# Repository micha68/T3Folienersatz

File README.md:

# T3_Leiterfolie_Ersatz
Ersetzt die Leiterfolie im Instrumententräger

In meinem Fall bei einer Pritsche Bj85, Turbodiesel mit dynamischer Ölkontrolle.

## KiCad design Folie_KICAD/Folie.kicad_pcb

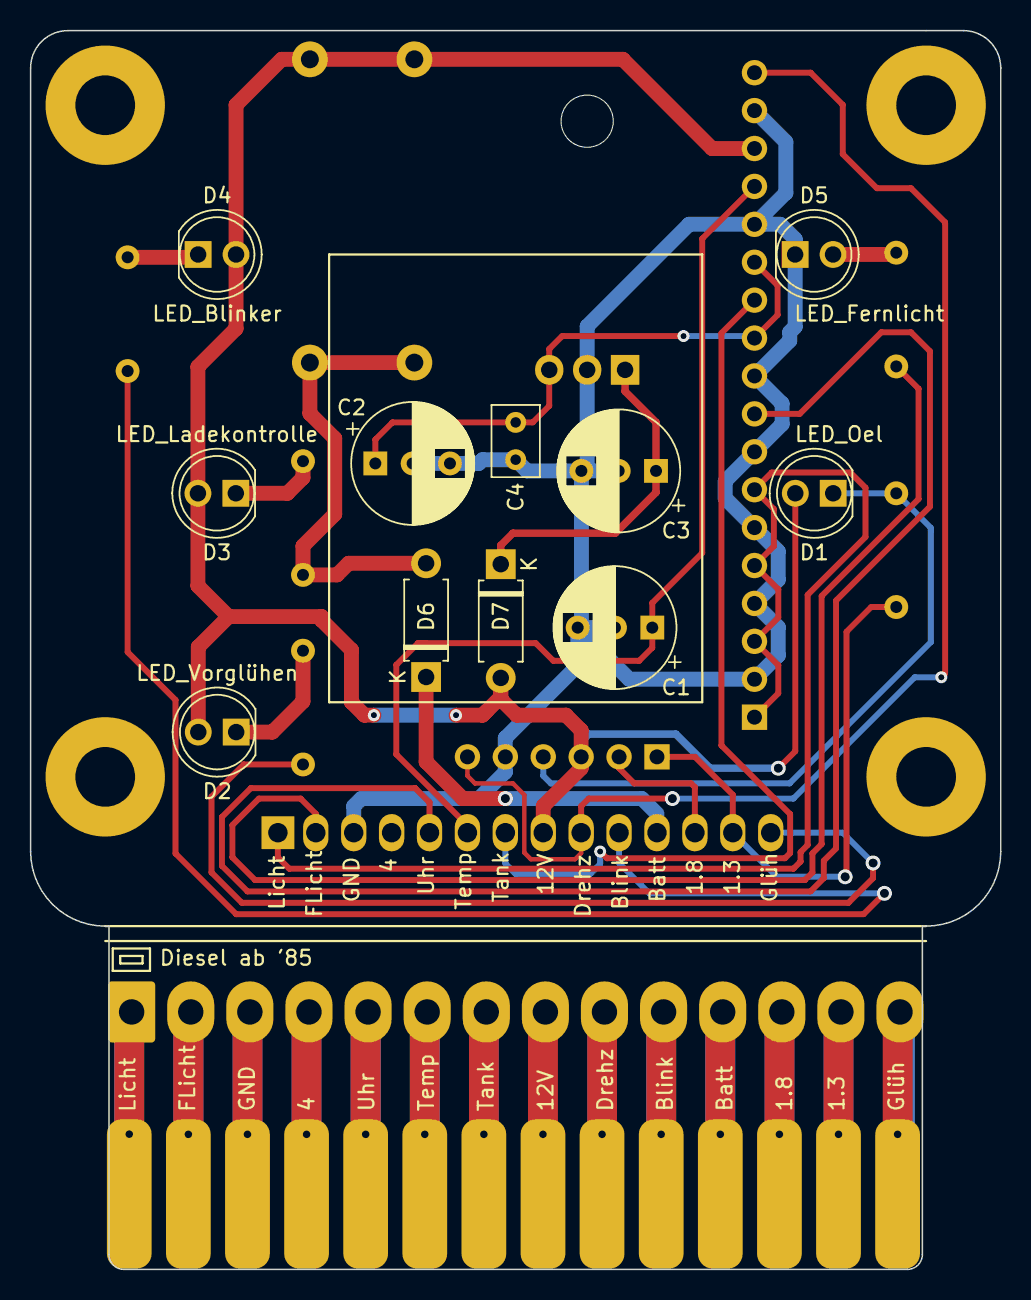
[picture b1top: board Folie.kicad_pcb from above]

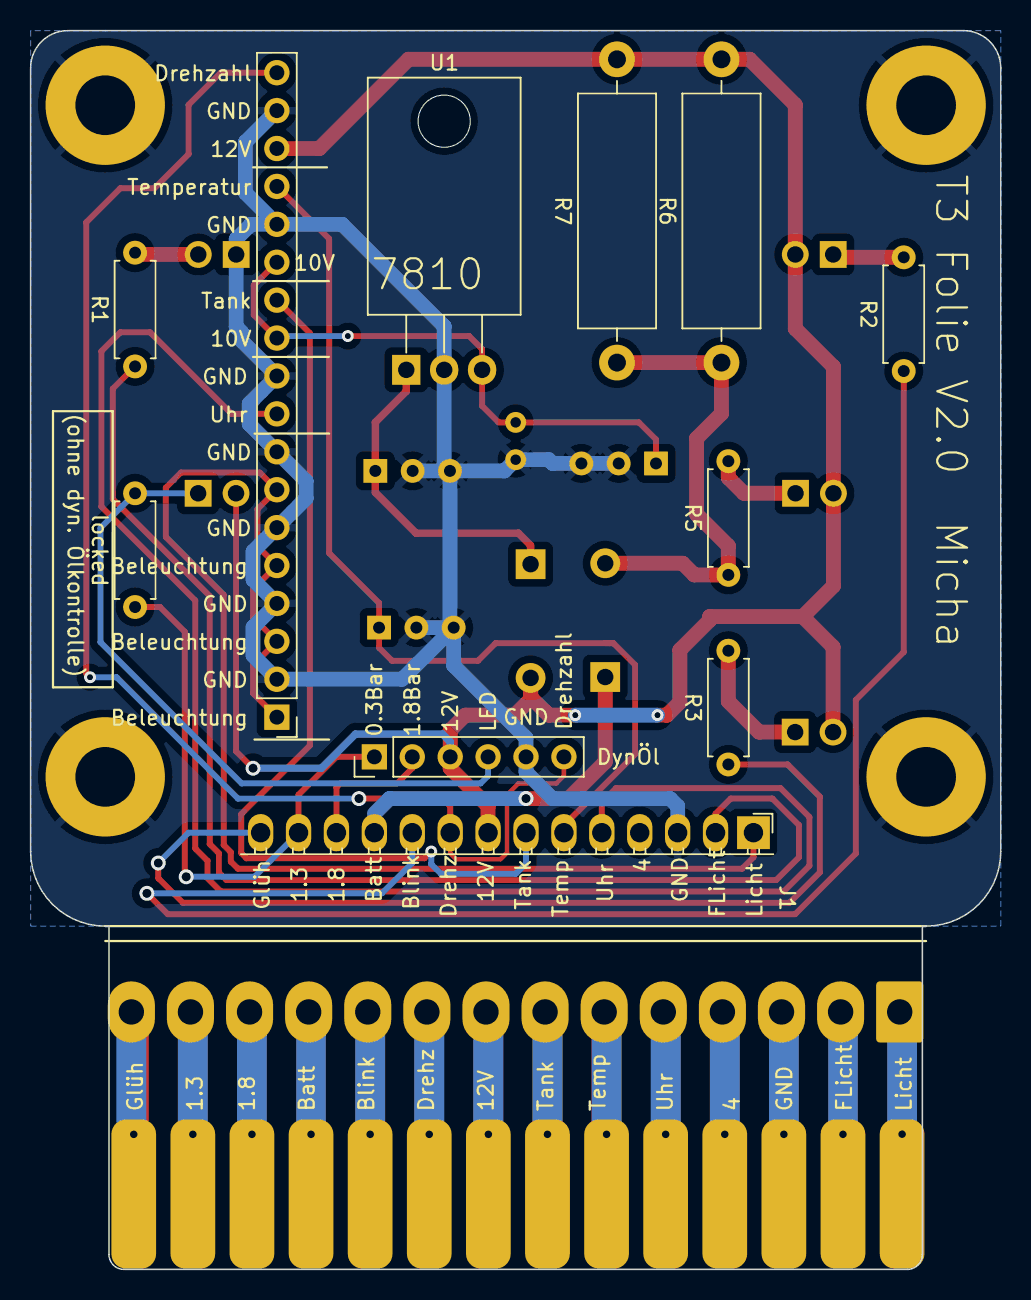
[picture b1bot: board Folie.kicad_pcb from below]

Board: 2 copper layers, 65.0 x 83.0 mm, 28 parts (11 on the bottom side), 22 nets.

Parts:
C1: 2,2u; CP_Radial_D8.0mm_P5.00mm
C2, C3: 35u; CP_Radial_D8.0mm_P5.00mm
C4: 100n; C_Rect_L4.6mm_W3.0mm_P2.50mm_MKS02_FKP02
D1: LED_Oel; LED_D5.0mm
D2: LED_Vorglühen; LED_D5.0mm
D3: LED_Ladekontrolle; LED_D5.0mm
D4: LED_Blinker; LED_D5.0mm
D5: LED_Fernlicht; LED_D5.0mm
D6, D7: 1N4007; D_A-405_P7.62mm_Horizontal
H1, H2, H3, H4: MountingHole; MountingHole_4mm_Pad
J1: Lötpunkte; PinHeader_1x14_P2.54mm_Horizontal
J2: Lötpunkte; Molex_KK-396_A-41791-0014_1x14_P3.96mm_Vertical
J3: Platinenkontakte; Molex_KK-396_A-41791-0014_1x14_P3.96mm_Vertical
J4: Conn_01x18; PinHeader_1x18_P2.54mm_Vertical
J5: DynÖl; PinHeader_1x06_P2.54mm_Vertical
R1, R2, R3, R5: R; R_Axial_DIN0207_L6.3mm_D2.5mm_P7.62mm_Horizontal
R6, R7: R120 2W; R_Axial_DIN0516_L15.5mm_D5.0mm_P20.32mm_Horizontal
U1: LM7810_TO220; TO-220-3_Horizontal_TabDown
locked: R; R_Axial_DIN0207_L6.3mm_D2.5mm_P7.62mm_Horizontal

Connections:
/0.3_Bar: J1.13, J2.13, J3.13, J5.1, locked.1
/1.8_Bar: J1.12, J2.12, J3.12, J5.2
/10V: C2.1, C4.1, J4.11, J4.13, U1.3 (VO)
/12V: D1.2 (A), D2.2 (A), D3.2 (A), D4.2 (A), D7.2 (A), J1.8, J2.8, J3.8, J4.16, J5.3, R6.2, R7.2
/Beleuchtung: J1.1, J2.1, J3.1, J4.1, J4.3, J4.5, J4.7
/Blinker: J1.10, J2.10, J3.10, R2.1
/Drehzahl: J1.9, J2.9, J3.9, J4.18, J5.6
/Dyn_Oeldruck: D1.1 (K), J5.4, locked.2
/Fernlicht: J1.2, J2.2, J3.2, R1.1
/Ladekontrolle: D6.1 (K), J1.11, J2.11, J3.11
/Tank: J1.7, J2.7, J3.7, J4.12
/Temperatur: C1.1, J1.6, J2.6, J3.6, J4.15
/Uhr: J1.5, J2.5, J3.5, J4.9
/Vorglühen: J1.14, J2.14, J3.14, R3.1
/pin4: J1.4, J2.4, J3.4
GND: C1.2, C2.2, C3.2, C4.2, D5.1 (K), H1.1, H2.1, H3.1, H4.1, J1.3, J2.3, J3.3, J4.2, J4.4, J4.6, J4.8, J4.10, J4.14, J4.17, J5.5, U1.2 (GND)
unnamed: D2.1 (K), R3.2
unnamed: D3.1 (K), R5.2
unnamed: D4.1 (K), R2.2
unnamed: D5.2 (A), R1.2
unnamed: D6.2 (A), R5.1, R6.1, R7.1
unnamed: C3.1, D7.1 (K), U1.1 (VI)
